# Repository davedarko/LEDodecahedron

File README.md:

# LEDodecahedron
 dodecahedron with LEDs

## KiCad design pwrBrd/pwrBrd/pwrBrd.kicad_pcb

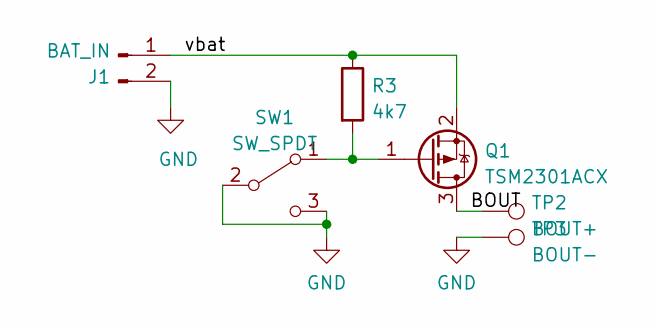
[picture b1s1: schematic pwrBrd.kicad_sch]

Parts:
J1: BAT_IN; JST_PH_S2B-PH-SM4-TB_1x02-1MP_P2.00mm_Horizontal
Q1: TSM2301ACX; SOT-23
R3: 4k7; R_0603_1608Metric_Pad0.98x0.95mm_HandSolder
SW1: SW_SPDT; SW_SPDT_PCM12
TP2: BOUT+; TestPoint_Pad_D1.5mm
TP3: BOUT-; TestPoint_Pad_D1.5mm

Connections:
/BOUT: Q1.3 (D), TP2.1
/vbat: J1.1, Q1.2 (S), R3.1
GND: J1.2, SW1.2 (B), SW1.3 (C), TP3.1
unnamed: Q1.1 (G), R3.2, SW1.1 (A)

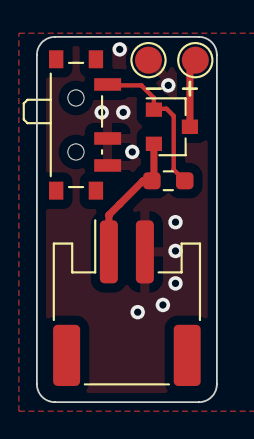
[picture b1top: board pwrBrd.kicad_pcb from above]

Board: 2 copper layers, 10.0 x 20.3 mm, 6 parts (0 on the bottom side), 4 nets.

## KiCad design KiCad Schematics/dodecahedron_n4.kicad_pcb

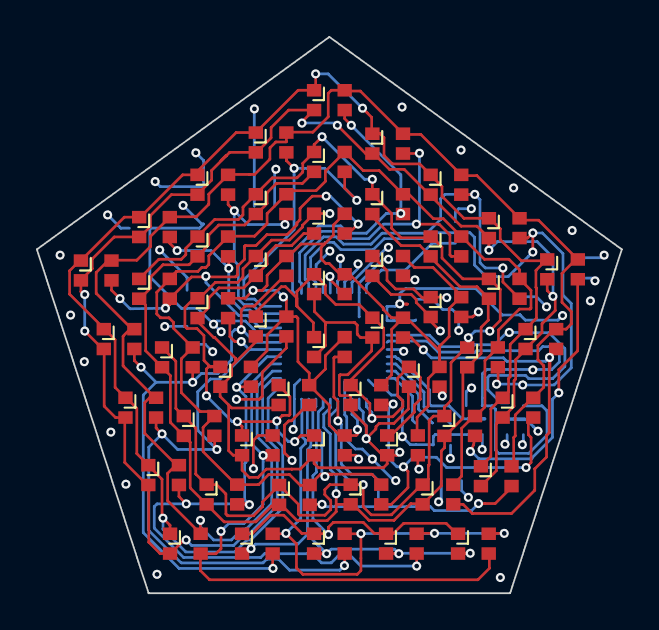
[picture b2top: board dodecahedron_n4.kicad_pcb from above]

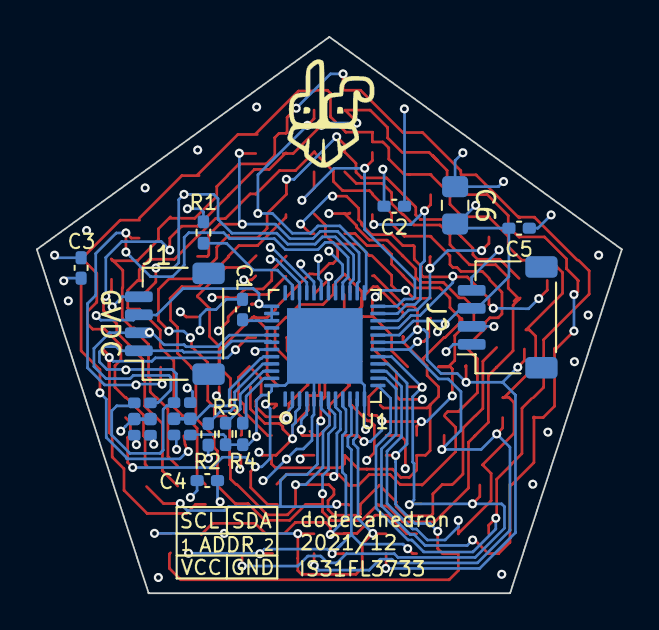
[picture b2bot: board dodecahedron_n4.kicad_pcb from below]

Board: 4 copper layers, 32.5 x 30.9 mm, 68 parts (16 on the bottom side), 38 nets.

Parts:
C1, C3: 470nF; C_0402_1005Metric_Pad0.74x0.62mm_HandSolder
C2, C4, C5: 100nF; C_0402_1005Metric_Pad0.74x0.62mm_HandSolder
C6: 1uF; C_0805_2012Metric_Pad1.18x1.45mm_HandSolder
D1, D2, D3, D4, D5, D6, D7, D8, D9, D10, D11, D12, D13, D14, D15, D16, D17, D18, D19, D20, D21, D22, D23, D24, D25, D26, D27, D28, D29, D30, D31, D32, D33, D34, D35, D36, D37, D38, D39, D40, D41, D42, D43, D44, D45, D46, D47, D48, D49, D50, D51: LED_RBGA; B2020RGBA
J1, J2: Conn_01x04_Female; JST_SH_SM04B-SRSS-TB_1x04-1MP_P1.00mm_Horizontal
R1: 20k; R_0402_1005Metric_Pad0.72x0.64mm_HandSolder
R2, R4, R5: 100k; R_0402_1005Metric_Pad0.72x0.64mm_HandSolder
U1: IS31FL3733-QF; QFN-48-1EP_6x6mm_P0.4mm_EP4.2x4.2mm
U2: Board; pentagon_deploy_cut
U3: Board; davedarko_logo_silk_outline
U4, U5: Jumper4; SolderJumper-4-0402

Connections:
/CS1: D11.4, D44.4, D51.4, U1.16
/CS2: D10.4, D43.4, D47.4, D50.4, U1.17
/CS3: D9.4, D34.4, D46.4, D49.4, U1.18
/CS4: D8.4, D33.4, D45.4, D48.4, U1.19
/CS5: D24.4, D37.4, D41.4, U1.21
/CS6: D23.4, D36.4, D40.4, U1.22
/CS7: D14.4, D35.4, D39.4, U1.23
/CS8: D13.4, D27.4, D38.4, U1.24
/CS9: D4.4, D26.4, D31.4, U1.25
/CS10: D3.4, D25.4, D30.4, U1.26
/CS11: D17.4, D29.4, D42.4, U1.27
/CS12: D16.4, D28.4, D32.4, U1.28
/CS13: D15.4, D21.4, D22.4, U1.30
/CS14: D7.4, D12.4, D20.4, U1.31
/CS15: D2.4, D6.4, D19.4, U1.32
/CS16: D1.4, D5.4, D18.4, U1.33
/I2C_RST: R4.2, U1.47
/INTB: R2.2, U1.45
/SDB: R5.2, U1.46
ADDR1: U1.43, U4.5
ADDR2: U1.44, U5.5
GND: C1.1, C2.1, C3.1, C4.1, C5.1, C6.1, J1.4, J2.4, R1.1, R4.1, R5.1, U1.5, U1.12, U1.34, U1.48, U1.49, U4.1, U5.1
unnamed: R1.2, U1.35
SCL: J1.1, J2.1, U1.42, U4.4, U5.4
SDA: J1.2, J2.2, U1.41, U4.3, U5.3
SW1: D1.1, D2.1, D3.1, D4.1, D12.1, D13.1, D14.1, D22.1, D23.1, D24.1, D32.1, D33.1, D34.1, D42.1, D43.1, D44.1, U1.2
SW2: D1.3, D2.3, D3.3, D4.3, D12.3, D13.3, D14.3, D22.3, D23.3, D24.3, D32.3, D33.3, D34.3, D42.3, D43.3, D44.3, U1.3
SW3: D1.2, D2.2, D3.2, D4.2, D12.2, D13.2, D14.2, D22.2, D23.2, D24.2, D32.2, D33.2, D34.2, D42.2, D43.2, D44.2, U1.4
SW4: D5.1, D6.1, D7.1, D15.1, D16.1, D17.1, D25.1, D26.1, D27.1, D35.1, D36.1, D37.1, D45.1, D46.1, D47.1, U1.6
SW5: D5.3, D6.3, D7.3, D15.3, D16.3, D17.3, D25.3, D26.3, D27.3, D35.3, D36.3, D37.3, D45.3, D46.3, D47.3, U1.7
SW6: D5.2, D6.2, D7.2, D15.2, D16.2, D17.2, D25.2, D26.2, D27.2, D35.2, D36.2, D37.2, D45.2, D46.2, D47.2, U1.8
SW7: D8.1, D9.1, D10.1, D11.1, U1.9
SW8: D8.3, D9.3, D10.3, D11.3, U1.10
SW9: D8.2, D9.2, D10.2, D11.2, U1.11
SW10: D18.1, D19.1, D20.1, D21.1, D28.1, D29.1, D30.1, D31.1, D38.1, D39.1, D40.1, D41.1, D48.1, D49.1, D50.1, D51.1, U1.13
SW11: D18.3, D19.3, D20.3, D21.3, D28.3, D29.3, D30.3, D31.3, D38.3, D39.3, D40.3, D41.3, D48.3, D49.3, D50.3, D51.3, U1.14
SW12: D18.2, D19.2, D20.2, D21.2, D28.2, D29.2, D30.2, D31.2, D38.2, D39.2, D40.2, D41.2, D48.2, D49.2, D50.2, D51.2, U1.15
VCC: C1.2, C2.2, C3.2, C4.2, C5.2, C6.2, J1.3, J2.3, R2.1, U1.20, U1.29, U1.37, U1.38, U1.39, U4.2, U5.2

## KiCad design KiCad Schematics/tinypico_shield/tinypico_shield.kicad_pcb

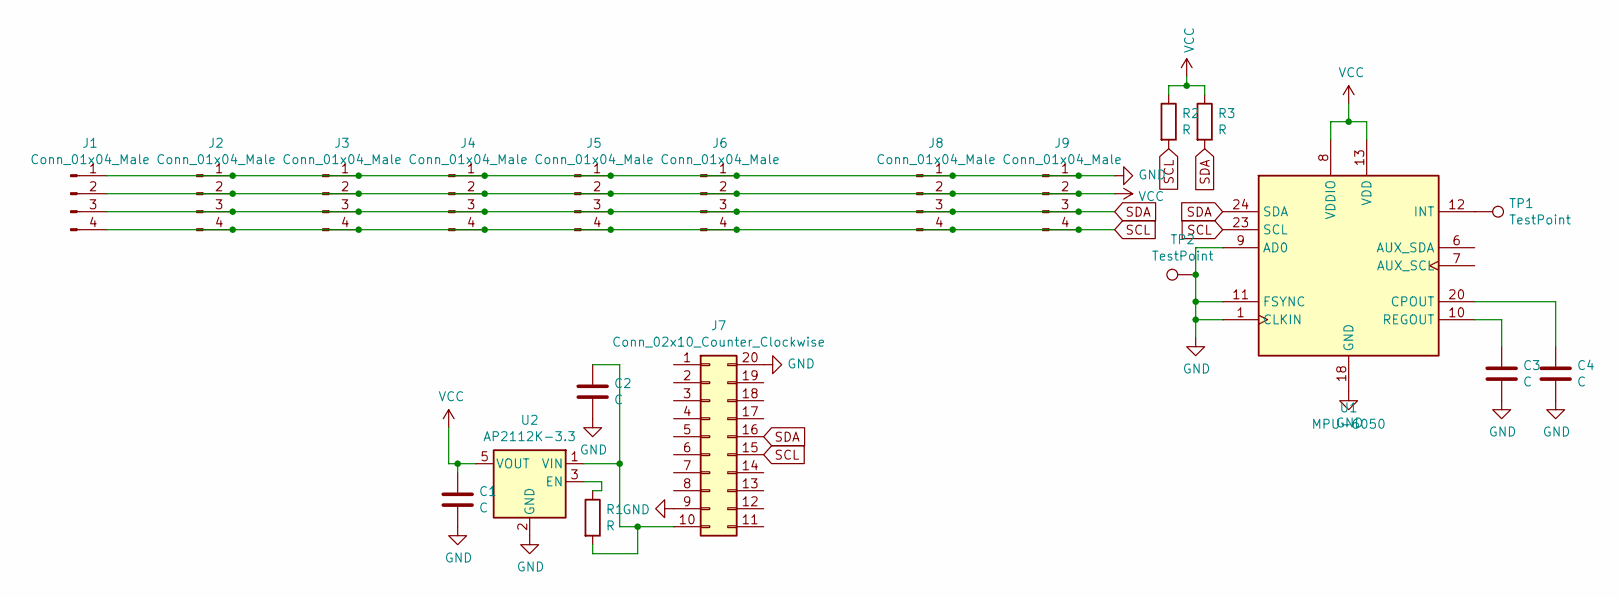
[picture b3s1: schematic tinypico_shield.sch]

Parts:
C1, C2, C3, C4: C; C_0402_1005Metric_Pad0.74x0.62mm_HandSolder
J1, J2, J3, J4, J5, J6: Conn_01x04_Male; JST_SH_BM04B-SRSS-TB_1x04-1MP_P1.00mm_Vertical
J7: Conn_02x10_Counter_Clockwise; TinyPico
J8, J9: Conn_01x04_Male; JST_SH_SM04B-SRSS-TB_1x04-1MP_P1.00mm_Horizontal
R1, R2, R3: R; R_0402_1005Metric_Pad0.72x0.64mm_HandSolder
TP1: TestPoint; TestPoint_Pad_D1.5mm
TP2: TestPoint; TestPoint_Pad_2.0x2.0mm
U1: MPU-6050; InvenSense_QFN-24_4x4mm_P0.5mm
U2: AP2112K-3.3; SOT-23-5

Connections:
GND: C1.2, C2.2, C3.2, C4.2, J1.1, J2.1, J3.1, J4.1, J5.1, J6.1, J7.9, J7.20, J8.1, J9.1, TP2.1, U1.1 (CLKIN), U1.9 (AD0), U1.11 (FSYNC), U1.18 (GND), U2.2 (GND)
unnamed: C2.1, J7.10, R1.2, U2.1 (VIN)
unnamed: C3.1, U1.10 (REGOUT)
unnamed: C4.1, U1.20 (CPOUT)
unnamed: R1.1, U2.3 (EN)
unnamed: TP1.1, U1.12 (INT)
SCL: J1.4, J2.4, J3.4, J4.4, J5.4, J6.4, J7.15, J8.4, J9.4, R2.2, U1.23 (SCL)
SDA: J1.3, J2.3, J3.3, J4.3, J5.3, J6.3, J7.16, J8.3, J9.3, R3.2, U1.24 (SDA)
VCC: C1.1, J1.2, J2.2, J3.2, J4.2, J5.2, J6.2, J8.2, J9.2, R2.1, R3.1, U1.8 (VDDIO), U1.13 (VDD), U2.5 (VOUT)

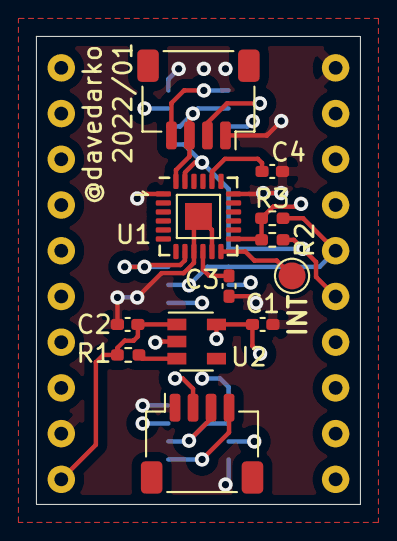
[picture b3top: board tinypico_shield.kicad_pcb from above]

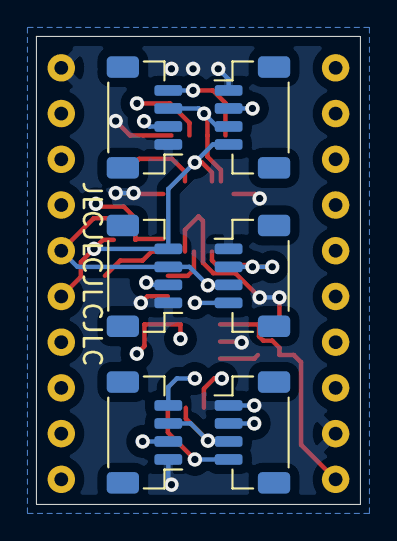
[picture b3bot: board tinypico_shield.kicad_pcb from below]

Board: 4 copper layers, 18.0 x 26.0 mm, 20 parts (6 on the bottom side), 9 nets.

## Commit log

2021-12-14 kicad files, bom n stuff
2021-12-14 moved files and final order
2021-12-14 3d files
2022-01-02 updated PCB
2022-01-02 updated 3d files
2022-08-21 kicad and case
2024-06-29 reworking lost progress
2024-06-29 gitignore
2024-06-29 more stuff
2024-06-30 cleaned up arduino code
